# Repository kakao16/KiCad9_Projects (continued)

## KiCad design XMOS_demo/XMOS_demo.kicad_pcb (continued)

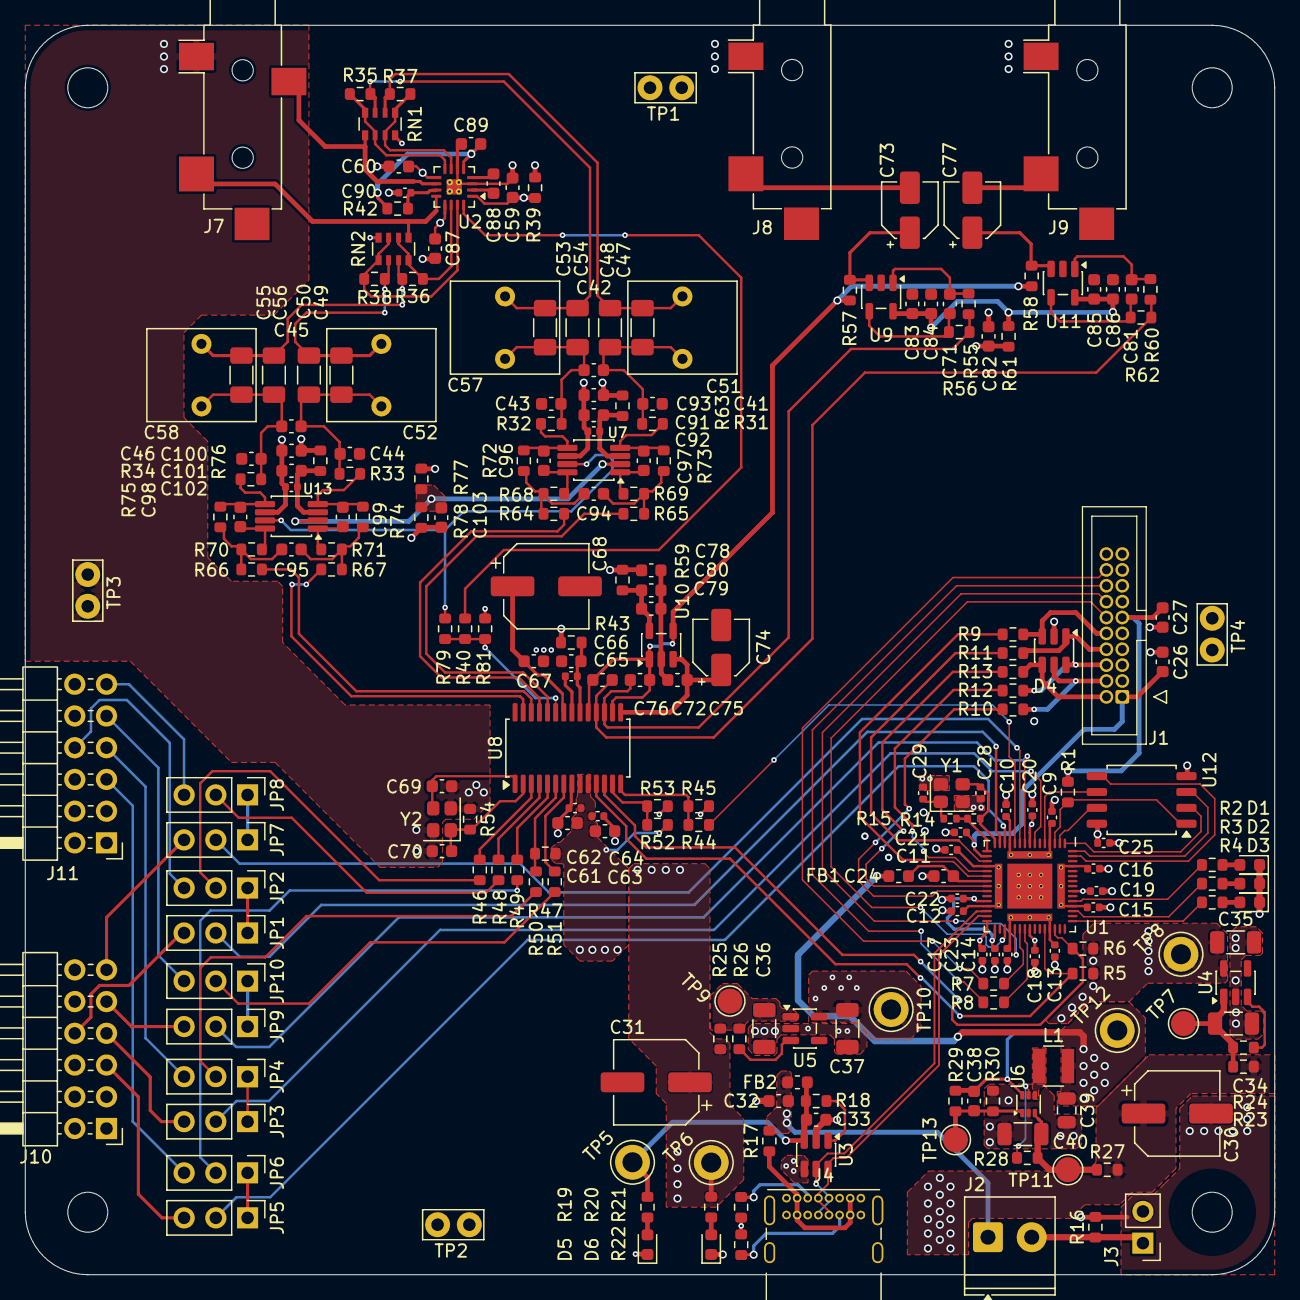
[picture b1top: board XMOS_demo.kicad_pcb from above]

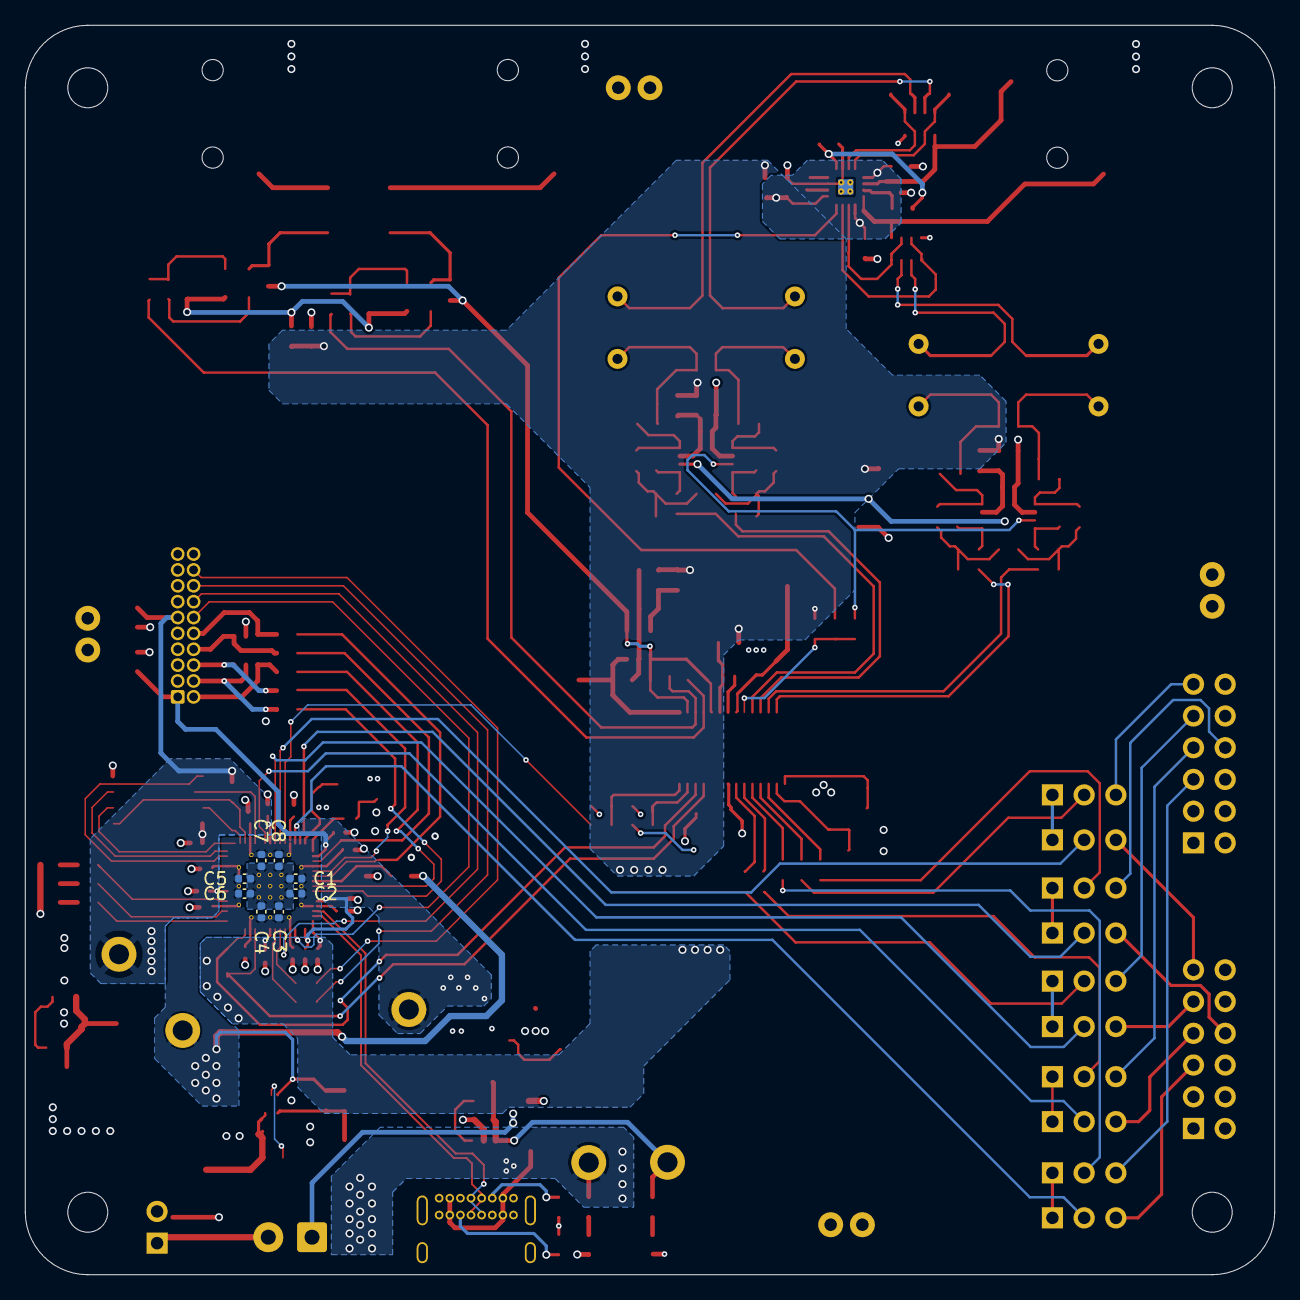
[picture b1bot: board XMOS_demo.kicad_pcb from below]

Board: 4 copper layers, 100.0 x 100.0 mm, 244 parts (8 on the bottom side), 150 nets.

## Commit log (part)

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2026-03-22 XMOS_demo initial, ignore
2026-03-23 crystal, usb
2026-03-25 leds, usb cc lines
2026-03-28 usb moved to seperate sch, power supply sch started
2026-03-29 sch work
2026-04-01 Work on audio output amplifier
2026-04-04 Lots of sch work
2026-04-04 sch work, pcb import and initial board outline
2026-04-06 terminal block for power input added
2026-04-11 sch mostly finished, needs tp, pcb component layout started
2026-04-12 finished sch, pcb work
2026-04-17 PCB work, changes for better routing
2026-05-03 sch work changes (jumpers, connectors, tp)
2026-05-03 merge
2026-05-03 pcb routing
2026-05-21 I2S config sch page added
2026-06-09 Summary (required)
2026-06-10 Started changes on power supply (audio in) on schematic
2026-06-11 Passive lpf added to autio output
2026-06-11 PCB work
2026-06-11 added simulation of audio output
2026-06-11 changed folder structure
2026-06-12 Changed flash to correct part
2026-06-14 routing work
2026-06-14 pdf documentation
2026-06-15 aktualizacja dokumentacji
2026-06-15 sch export
